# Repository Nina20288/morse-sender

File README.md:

# morse-sender
A small device where I can type morse code and then send it to a computer or another device.

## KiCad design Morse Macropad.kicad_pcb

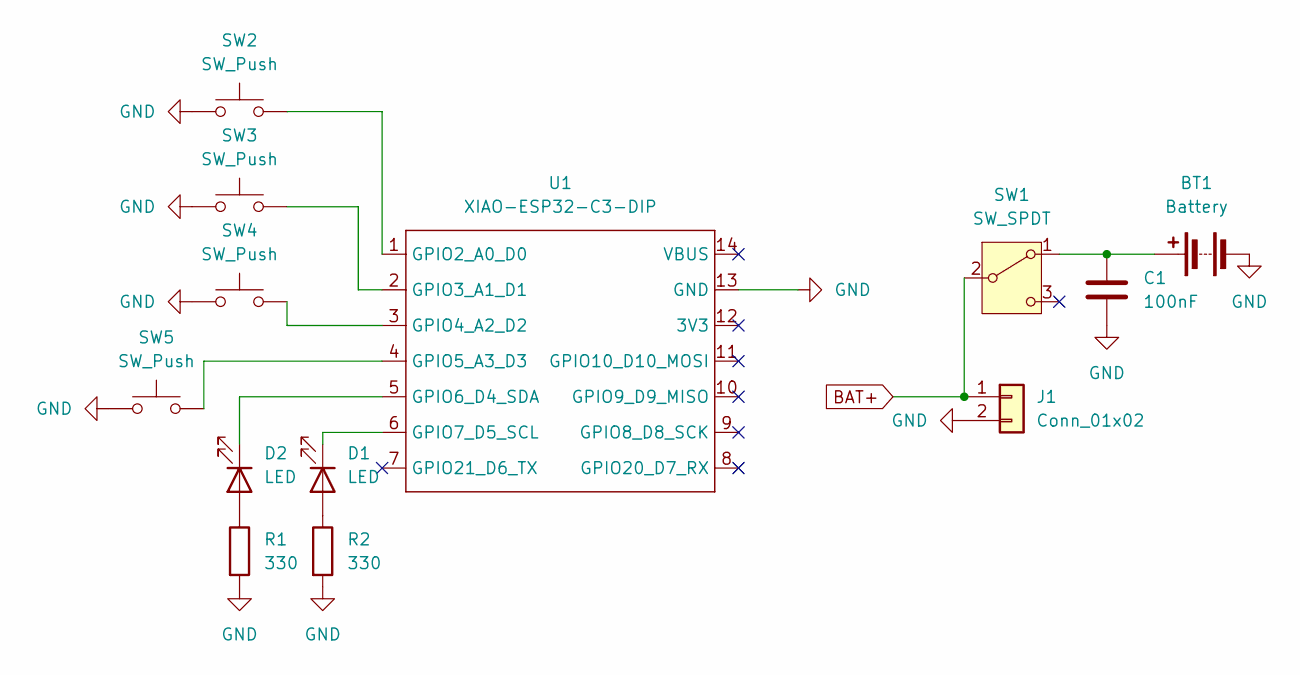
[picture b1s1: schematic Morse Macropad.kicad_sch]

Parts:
BT1: Battery
C1: 100nF; C_0805_2012Metric
D1, D2: LED; LED_0805_2012Metric
J1: Conn_01x02; JST_GH_SM02B-GHS-TB_1x02-1MP_P1.25mm_Horizontal
R1, R2: 330; R_0805_2012Metric
SW1: SW_SPDT; SW_Slide_SP3T_Straight_CK_OS103012MU1QP1
SW2, SW3, SW4, SW5: SW_Push; SW_Push_1TS009xxxx-xxxx-xxxx_6x6x5mm
U1: XIAO-ESP32-C3-DIP; XIAO-ESP32-C3-DIP-SMD

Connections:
BAT+: J1.1, SW1.2 (B)
GND: BT1.2 (-), C1.2, J1.2, R1.2, R2.2, SW2.1, SW3.1, SW4.1, SW5.1, U1.13 (GND)
unnamed: BT1.1 (+), C1.1, SW1.1 (A)
unnamed: D1.2 (A), R2.1
unnamed: D1.1 (K), U1.6 (GPIO7_D5_SCL)
unnamed: D2.2 (A), R1.1
unnamed: D2.1 (K), U1.5 (GPIO6_D4_SDA)
unnamed: SW2.2, U1.1 (GPIO2_A0_D0)
unnamed: SW3.2, U1.2 (GPIO3_A1_D1)
unnamed: SW4.2, U1.3 (GPIO4_A2_D2)
unnamed: SW5.2, U1.4 (GPIO5_A3_D3)

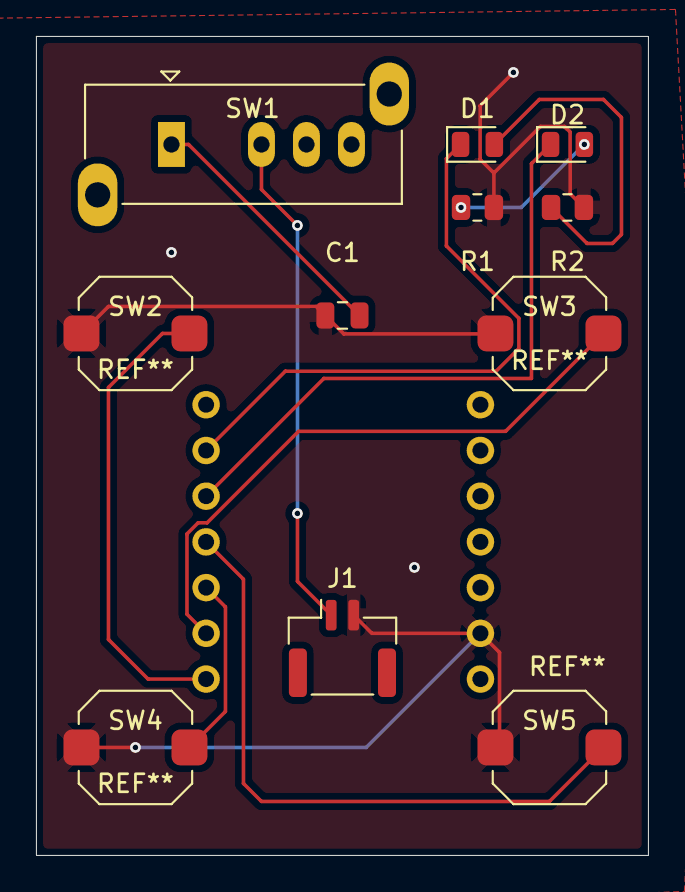
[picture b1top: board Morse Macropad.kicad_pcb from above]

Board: 2 copper layers, 34.0 x 45.5 mm, 12 parts (1 on the bottom side), 11 nets.

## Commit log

2026-05-04 images
2026-05-04 Include images of the morse sender device
    Added images of the device to the README.
2026-05-07 start organizing files
